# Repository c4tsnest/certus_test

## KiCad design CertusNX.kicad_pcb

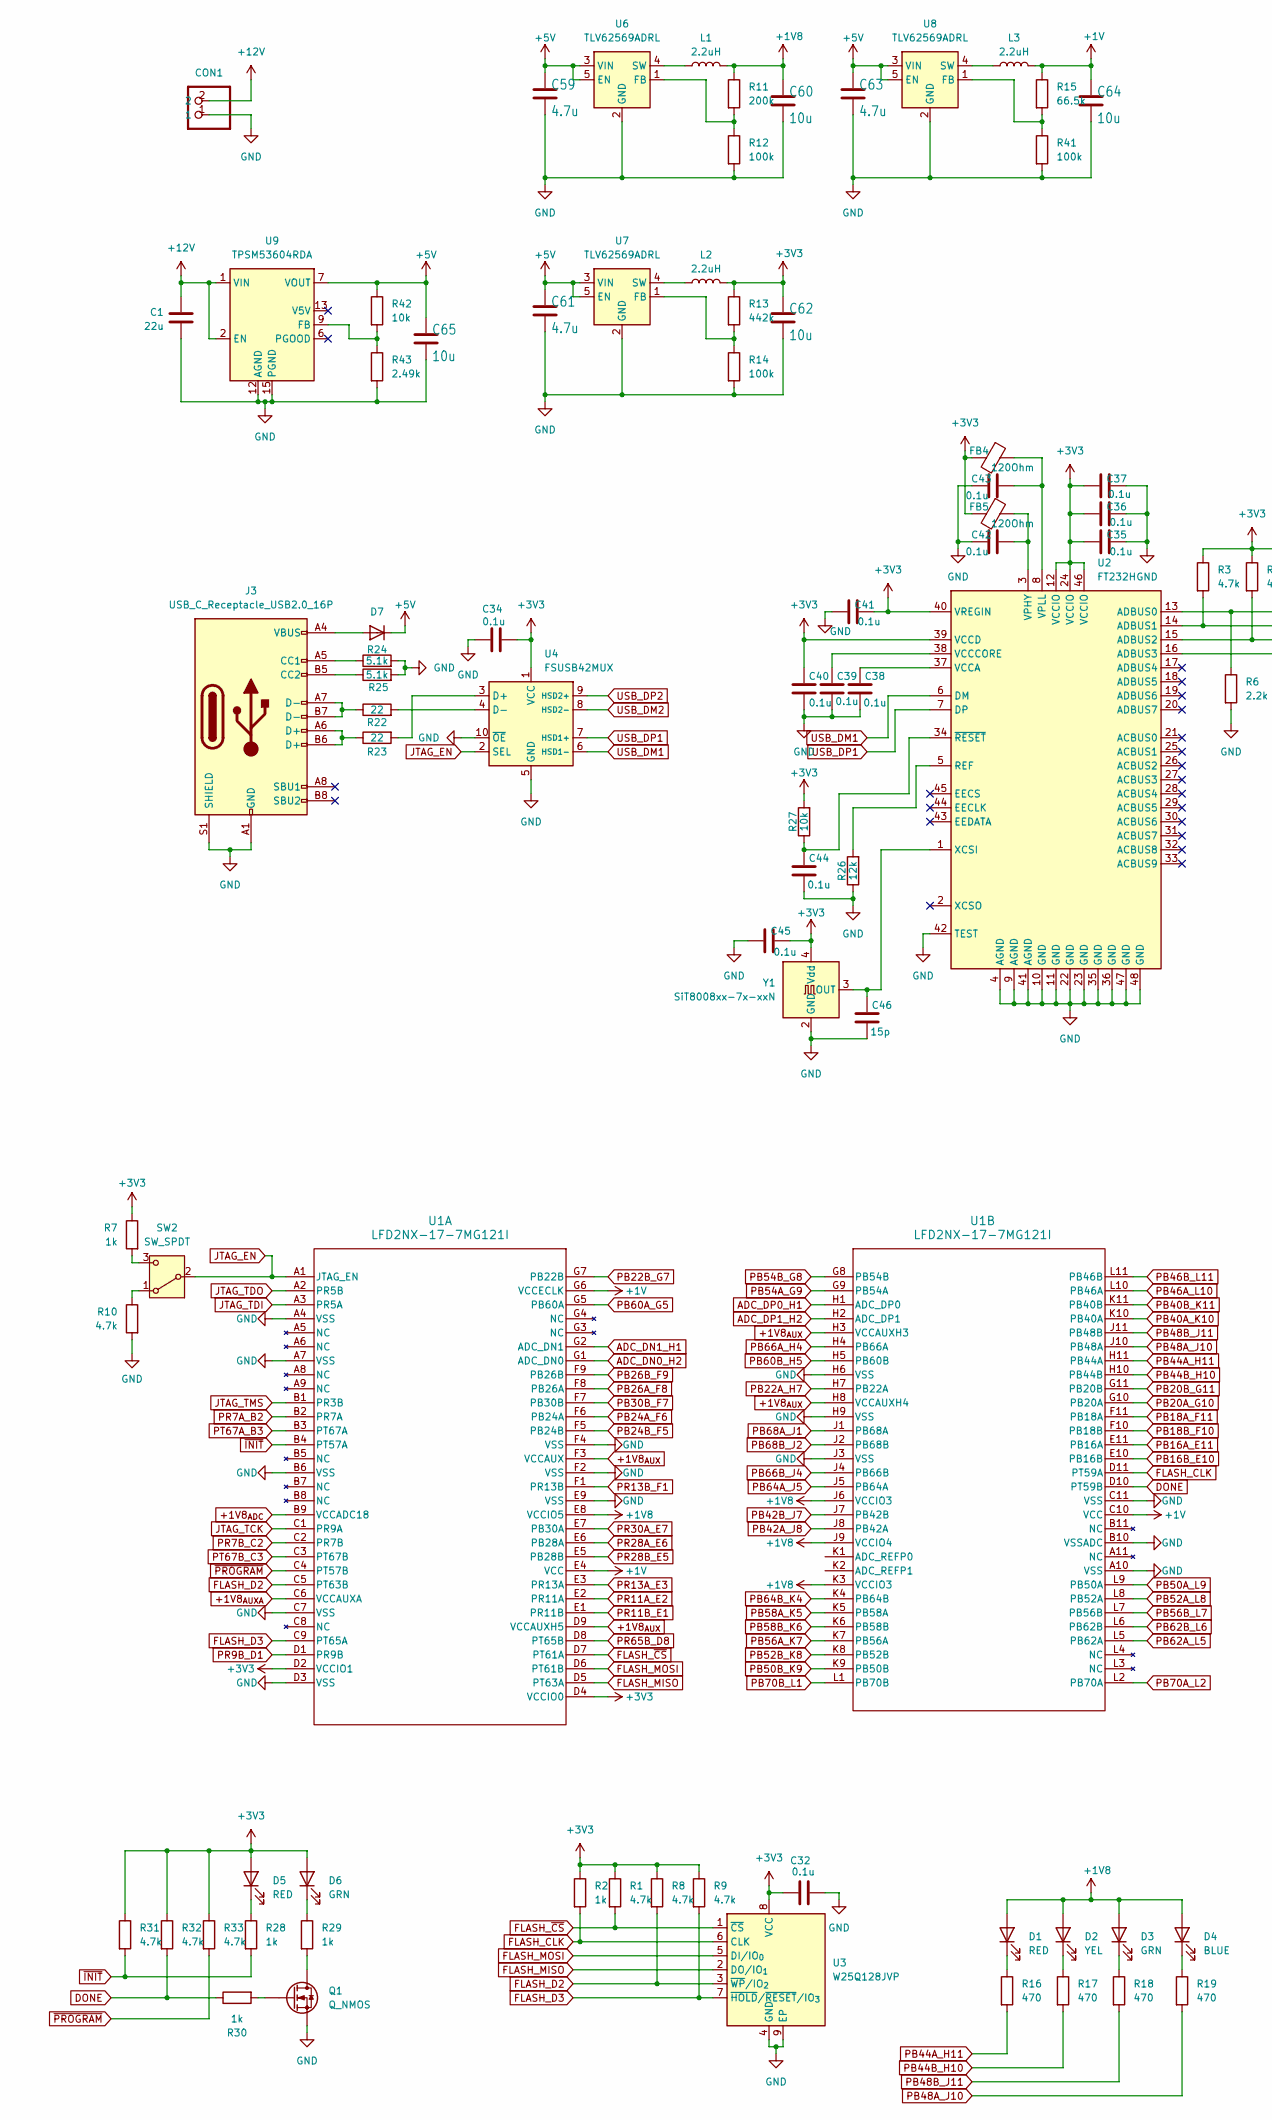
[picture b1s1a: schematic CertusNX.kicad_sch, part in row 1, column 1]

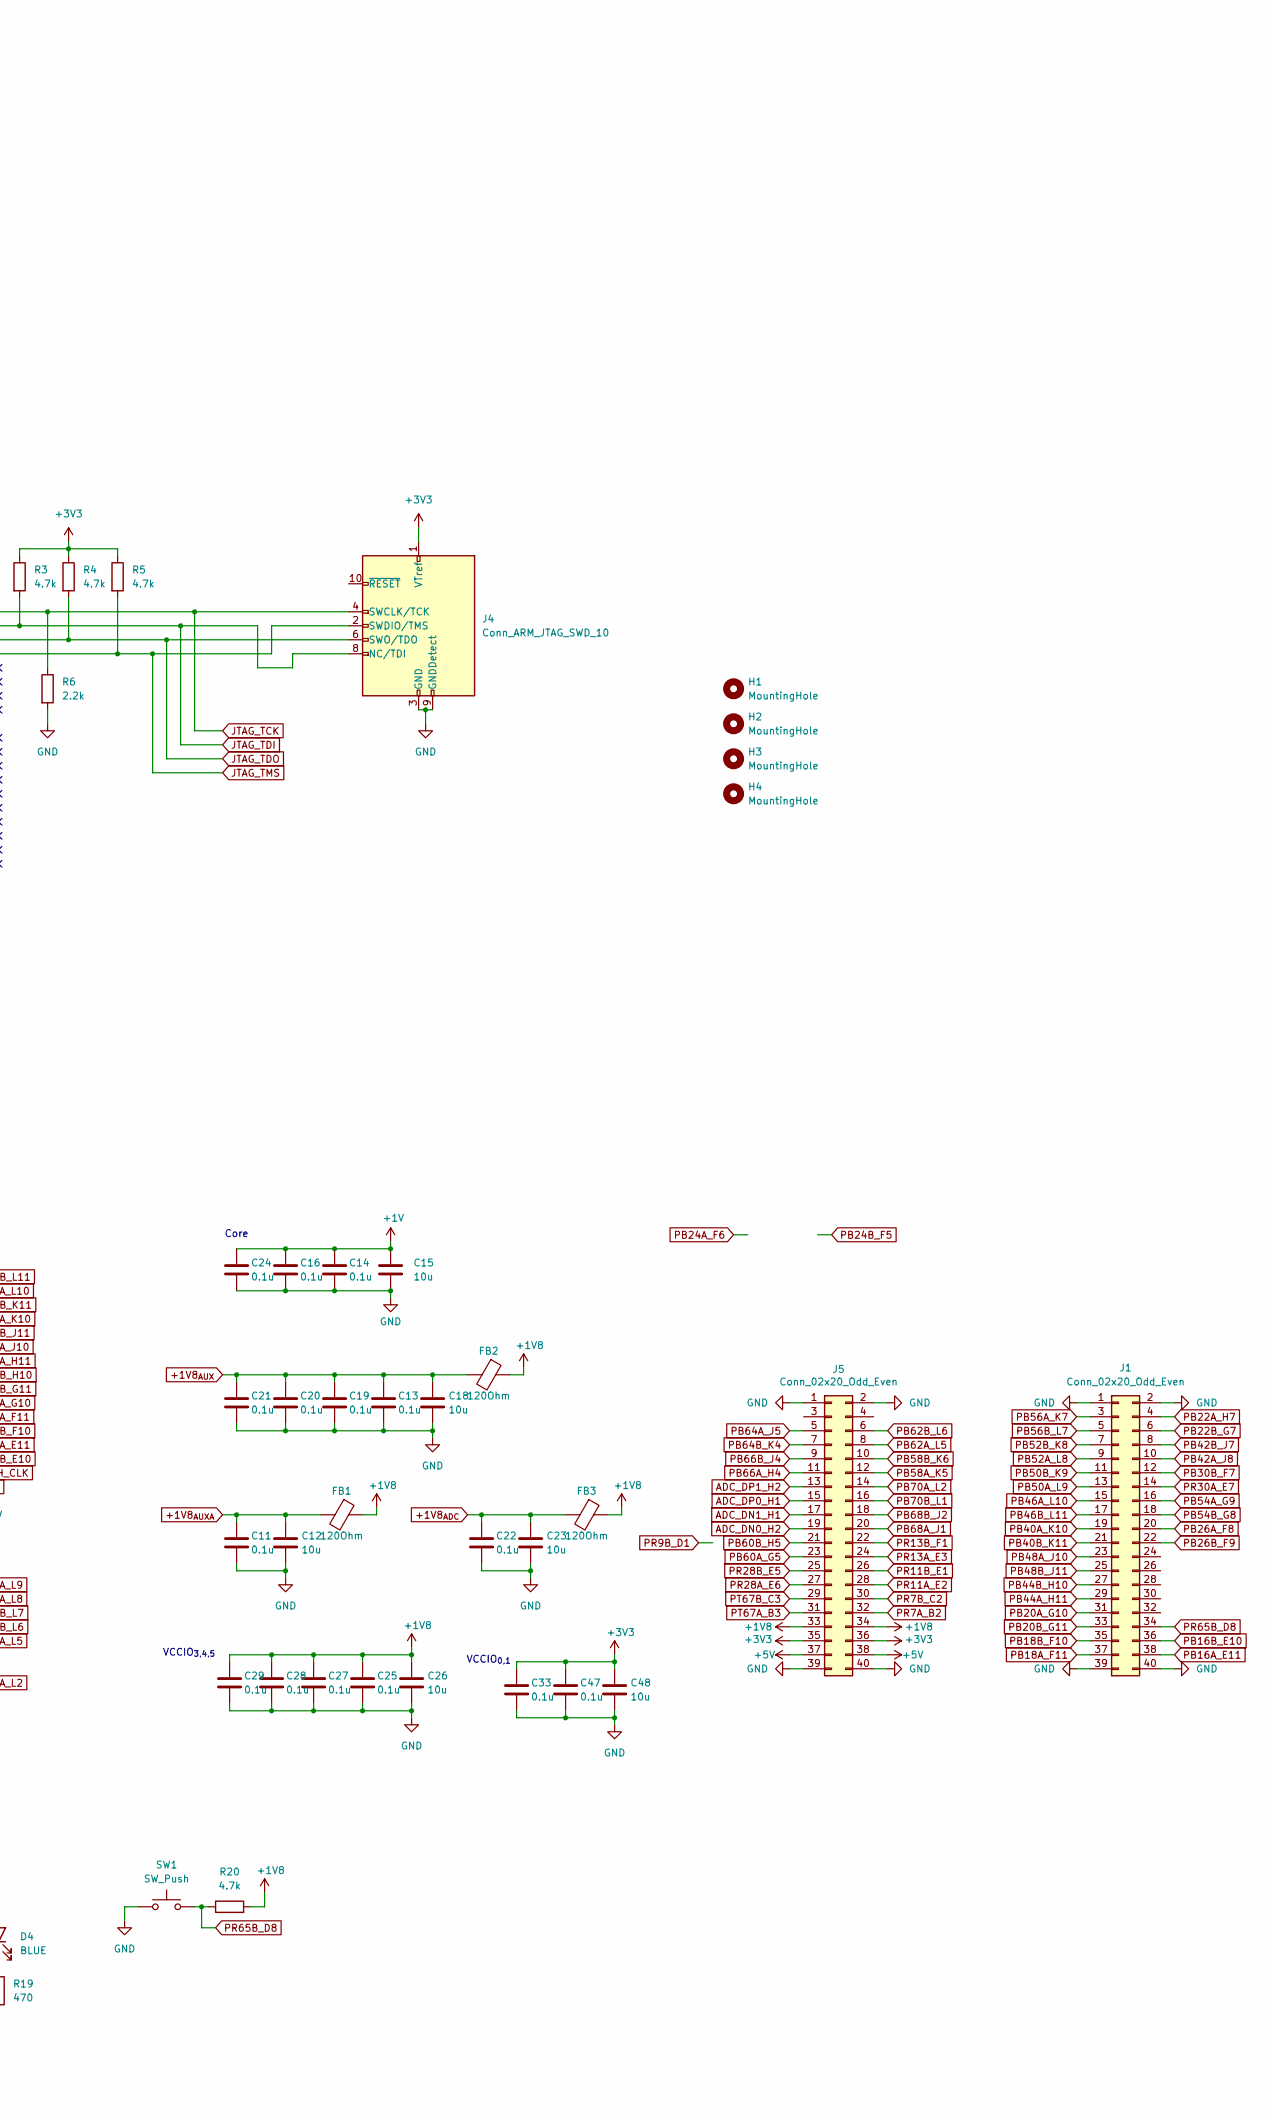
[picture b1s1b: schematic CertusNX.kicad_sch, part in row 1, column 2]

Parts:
C1: 22u; C_1206_3216Metric_Pad1.33x1.80mm_HandSolder
C11, C13, C14, C16, C19, C20, C21, C22, C24, C25, C27, C28, C29, C33, C47: 0.1u; C_0201_0603Metric
C12, C15, C18, C23, C26, C48, C60, C62, C64, C65: 10u; C_0603_1608Metric_Pad1.08x0.95mm_HandSolder
C32, C34, C35, C36, C37, C38, C39, C40, C41, C42, C43, C44, C45: 0.1u; C_0402_1005Metric_Pad0.74x0.62mm_HandSolder
C46: 15p; C_0402_1005Metric_Pad0.74x0.62mm_HandSolder
C59, C61, C63: 4.7u; C_0603_1608Metric_Pad1.08x0.95mm_HandSolder
CON1: Molex_Nano-Fit_105309-xx02_1x02_P2.50mm_Vertical
D1, D5: RED; LED_0402_1005Metric_Pad0.77x0.64mm_HandSolder
D2: YEL; LED_0402_1005Metric_Pad0.77x0.64mm_HandSolder
D3, D6: GRN; LED_0402_1005Metric_Pad0.77x0.64mm_HandSolder
D4: BLUE; LED_0402_1005Metric_Pad0.77x0.64mm_HandSolder
D7: SOD-123
FB1, FB2, FB3, FB4, FB5: 120Ohm; L_0603_1608Metric_Pad1.05x0.95mm_HandSolder
H1, H2, H3, H4: MountingHole; MountingHole_3.2mm_M3
J1, J5: Conn_02x20_Odd_Even; Molex_SlimStack_52991-0408_2x20_P0.50mm_Vertical
J3: USB_C_Receptacle_USB2.0_16P; USB_C_Receptacle_GCT_USB4105-xx-A_16P_TopMnt_Horizontal
J4: Conn_ARM_JTAG_SWD_10; PinHeader_2x05_P1.27mm_Vertical
L1, L2, L3: 2.2uH; L_1210_3225Metric_Pad1.42x2.65mm_HandSolder
Q1: Q_NMOS; SOT-416
R1, R3, R4, R5, R8, R9, R10, R20, R31, R32, R33: 4.7k; R_0402_1005Metric_Pad0.72x0.64mm_HandSolder
R2, R7, R28, R29, R30: 1k; R_0402_1005Metric_Pad0.72x0.64mm_HandSolder
R6: 2.2k; R_0402_1005Metric_Pad0.72x0.64mm_HandSolder
R11: 200k; R_0402_1005Metric_Pad0.72x0.64mm_HandSolder
R12, R14, R41: 100k; R_0402_1005Metric_Pad0.72x0.64mm_HandSolder
R13: 442k; R_0402_1005Metric_Pad0.72x0.64mm_HandSolder
R15: 66.5k; R_0402_1005Metric_Pad0.72x0.64mm_HandSolder
R16, R17, R18, R19: 470; R_0402_1005Metric_Pad0.72x0.64mm_HandSolder
R22, R23: 22; R_0402_1005Metric_Pad0.72x0.64mm_HandSolder
R24, R25: 5.1k; R_0402_1005Metric_Pad0.72x0.64mm_HandSolder
R26: 12k; R_0402_1005Metric_Pad0.72x0.64mm_HandSolder
R27, R42: 10k; R_0402_1005Metric_Pad0.72x0.64mm_HandSolder
R43: 2.49k; R_0402_1005Metric_Pad0.72x0.64mm_HandSolder
SW1: SW_Push; SW_SPST_B3U-1000P
SW2: SW_SPDT; SW_SPDT_PCM12
U1: LFD2NX-17-7MG121I
U2: FT232H; QFN-48-1EP_8x8mm_P0.5mm_EP6.2x6.2mm
U3: W25Q128JVP; WSON-8-1EP_6x5mm_P1.27mm_EP3.4x4.3mm
U4: FSUSB42MUX; FSUSB42UMX
U6, U7, U8: TLV62569ADRL; SOT-563
U9: TPSM53604RDA; Texas_B3QFN-14-1EP_5x5.5mm_P0.65mm_ThermalVia
Y1: SiT8008xx-7x-xxN; Oscillator_SMD_SiT_PQFN-4Pin_2.0x1.6mm

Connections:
+1V: C14.1, C15.1, C16.1, C24.1, C64.1, L3.2, R15.1, U1.C10 (VCC), U1.E4 (VCC), U1.G6 (VCCECLK)
+1V8: C25.1, C26.1, C27.1, C28.1, C29.1, C60.1, D1.2 (A), D2.2 (A), D3.2 (A), D4.2 (A), FB1.1, FB2.1, FB3.1, J5.33, J5.34, L1.2, R11.1, R20.2, U1.E8 (VCCIO5), U1.J6 (VCCIO3), U1.J9 (VCCIO4), U1.K3 (VCCIO3)
+1V8_{ADC}: C22.1, C23.1, FB3.2, U1.B9 (VCCADC18)
+1V8_{AUXA}: C11.1, C12.1, FB1.2, U1.C6 (VCCAUXA)
+1V8_{AUX}: C13.1, C18.1, C19.1, C20.1, C21.1, FB2.2, U1.D9 (VCCAUXH5), U1.F3 (VCCAUX), U1.H3 (VCCAUXH3), U1.H8 (VCCAUXH4)
+3V3: C32.1, C33.1, C34.2, C35.1, C36.1, C37.1, C40.1, C41.2, C45.2, C47.1, C48.1, C62.1, D5.2 (A), D6.2 (A), FB4.2, FB5.2, J4.1 (VTref), J5.35, J5.36, L2.2, R1.1, R2.1, R3.1, R4.1, R5.1, R7.1, R8.1, R9.1, R13.1, R27.2, R31.1, R32.1, R33.1, U1.D2 (VCCIO1), U1.D4 (VCCIO0), U2.12 (VCCIO), U2.24 (VCCIO), U2.39 (VCCD), U2.40 (VREGIN), U2.46 (VCCIO), U3.8 (VCC), U4.1 (VCC), Y1.4 (Vdd)
+5V: C59.1, C61.1, C63.1, C65.1, D7.K (C), J5.37, J5.38, R42.1, U6.3 (VIN), U6.5 (EN), U7.3 (VIN), U7.5 (EN), U8.3 (VIN), U8.5 (EN), U9.7 (VOUT), U9.8 (VOUT)
+12V: C1.1, CON1.2, U9.1 (VIN), U9.2 (EN), U9.14 (VIN)
ADC_DN0_H2: J5.19, U1.G1 (ADC_DN0)
ADC_DN1_H1: J5.17, U1.G2 (ADC_DN1)
ADC_DP0_H1: J5.15, U1.H1 (ADC_DP0)
ADC_DP1_H2: J5.13, U1.H2 (ADC_DP1)
DONE: R30.1, R32.2, U1.D10 (PT59B)
FLASH_CLK: R2.2, U1.D11 (PT59A), U3.6 (CLK)
FLASH_D2: R8.2, U1.C5 (PT63B), U3.3 (~WP/IO_{2})
FLASH_D3: R9.2, U1.C9 (PT65A), U3.7 (~HOLD/~RESET/IO_{3})
FLASH_MISO: U1.D5 (PT63A), U3.2 (DO/IO_{1})
FLASH_MOSI: U1.D6 (PT61B), U3.5 (DI/IO_{0})
FLASH_~CS: R1.2, U1.D7 (PT61A), U3.1 (~CS)
GND: C1.2, C11.2, C12.2, C13.2, C14.2, C15.2, C16.2, C18.2, C19.2, C20.2, C21.2, C22.2, C23.2, C24.2, C25.2, C26.2, C27.2, C28.2, C29.2, C32.2, C33.2, C34.1, C35.2, C36.2, C37.2, C38.2, C39.2, C40.2, C41.1, C42.2, C43.2, C44.2, C45.1, C46.2, C47.2, C48.2, C59.2, C60.2, C61.2, C62.2, C63.2, C64.2, C65.2, CON1.1, J1.1, J1.2, J1.39, J1.40, J3.A1 (GND), J3.A12 (GND), J3.B1 (GND), J3.B12 (GND), J3.S1 (SHIELD), J4.3 (GND), J4.5 (GND), J4.9 (GNDDetect), J5.1, J5.2, J5.39, J5.40, Q1.2 (S), Q1.S, R6.2, R10.2, R12.2, R14.2, R24.2, R25.2, R26.1, R41.2, R43.2, SW1.1, U1.A4 (VSS), U1.A7 (VSS), U1.A10 (VSS), U1.B6 (VSS), U1.B10 (VSSADC), U1.C7 (VSS), U1.C11 (VSS), U1.D3 (VSS), U1.E9 (VSS), U1.F2 (VSS), U1.F4 (VSS), U1.H6 (VSS), U1.H9 (VSS), U1.J3 (VSS), U2.4 (AGND), U2.9 (AGND), U2.10 (GND), U2.11 (GND), U2.22 (GND), U2.23 (GND), U2.35 (GND), U2.36 (GND), U2.41 (AGND), U2.42 (TEST), U2.47 (GND), U2.48 (GND), U3.4 (GND), U3.9 (EP), U4.5 (GND), U4.10 (~OE), U6.2 (GND), U7.2 (GND), U8.2 (GND), U9.3 (PGND), U9.10 (PGND), U9.11 (PGND), U9.12 (AGND), U9.15 (PGND), Y1.2 (GND)
JTAG_EN: SW2.2 (B), U1.A1 (JTAG_EN), U4.2 (SEL)
JTAG_TCK: J4.4 (SWCLK/TCK), R6.1, U1.C1 (PR9A), U2.13 (ADBUS0)
JTAG_TDI: J4.8 (NC/TDI), R3.2, U1.A3 (PR5A), U2.14 (ADBUS1)
JTAG_TDO: J4.6 (SWO/TDO), R4.2, U1.A2 (PR5B), U2.15 (ADBUS2)
JTAG_TMS: J4.2 (SWDIO/TMS), R5.2, U1.B1 (PR3B), U2.16 (ADBUS3)
unnamed: D1.1 (K), R16.1
unnamed: D2.1 (K), R17.1
unnamed: D3.1 (K), R18.1
unnamed: D4.1 (K), R19.1
unnamed: D5.1 (K), R28.1
unnamed: D6.1 (K), R29.1
unnamed: D7.A, J3.A4 (VBUS), J3.A9 (VBUS), J3.B4 (VBUS), J3.B9 (VBUS)
unnamed: J3.A5 (CC1), R24.1
unnamed: J3.B5 (CC2), R25.1
unnamed: J3.A6 (D+), J3.B6 (D+), R23.1
unnamed: J3.A7 (D-), J3.B7 (D-), R22.1
unnamed: Q1.3 (D), Q1.D, R29.2
unnamed: Q1.1 (G), Q1.G, R30.2
unnamed: R10.1, SW2.1 (A)
unnamed: R7.2, SW2.3 (C)
unnamed: R26.2, U2.5 (REF)
unnamed: C38.1, U2.37 (VCCA)
unnamed: C39.1, U2.38 (VCCCORE)
unnamed: C42.1, FB5.1, U2.3 (VPHY)
unnamed: C43.1, FB4.1, U2.8 (VPLL)
unnamed: C46.1, U2.1 (XCSI), Y1.3 (OUT)
unnamed: C44.1, R27.1, U2.34 (~RESET)
unnamed: R23.2, U4.3 (D+)
unnamed: R22.2, U4.4 (D-)
unnamed: R11.2, R12.1, U6.1 (FB)
unnamed: L1.1, U6.4 (SW)
unnamed: R13.2, R14.1, U7.1 (FB)
unnamed: L2.1, U7.4 (SW)
unnamed: R15.2, R41.1, U8.1 (FB)
unnamed: L3.1, U8.4 (SW)
unnamed: R42.2, R43.1, U9.9 (FB)
PB16A_E11: J1.38, U1.E11 (PB16A)
PB16B_E10: J1.36, U1.E10 (PB16B)
PB18A_F11: J1.37, U1.F11 (PB18A)
PB18B_F10: J1.35, U1.F10 (PB18B)
PB20A_G10: J1.31, U1.G10 (PB20A)
PB20B_G11: J1.33, U1.G11 (PB20B)
PB22A_H7: J1.4, U1.H7 (PB22A)
PB22B_G7: J1.6, U1.G7 (PB22B)
PB24A_F6: U1.F6 (PB24A)
PB24B_F5: U1.F5 (PB24B)
PB26A_F8: J1.20, U1.F8 (PB26A)
PB26B_F9: J1.22, U1.F9 (PB26B)
PB30B_F7: J1.12, U1.F7 (PB30B)
PB40A_K10: J1.19, U1.K10 (PB40A)
PB40B_K11: J1.21, U1.K11 (PB40B)
PB42A_J8: J1.10, U1.J8 (PB42A)
PB42B_J7: J1.8, U1.J7 (PB42B)
PB44A_H11: J1.29, R16.2, U1.H11 (PB44A)
PB44B_H10: J1.27, R17.2, U1.H10 (PB44B)
PB46A_L10: J1.15, U1.L10 (PB46A)
PB46B_L11: J1.17, U1.L11 (PB46B)
PB48A_J10: J1.23, R19.2, U1.J10 (PB48A)
PB48B_J11: J1.25, R18.2, U1.J11 (PB48B)
PB50A_L9: J1.13, U1.L9 (PB50A)
PB50B_K9: J1.11, U1.K9 (PB50B)
PB52A_L8: J1.9, U1.L8 (PB52A)
PB52B_K8: J1.7, U1.K8 (PB52B)
PB54A_G9: J1.16, U1.G9 (PB54A)
PB54B_G8: J1.18, U1.G8 (PB54B)
PB56A_K7: J1.3, U1.K7 (PB56A)
PB56B_L7: J1.5, U1.L7 (PB56B)
PB58A_K5: J5.12, U1.K5 (PB58A)
PB58B_K6: J5.10, U1.K6 (PB58B)
PB60A_G5: J5.23, U1.G5 (PB60A)
PB60B_H5: J5.21, U1.H5 (PB60B)
PB62A_L5: J5.8, U1.L5 (PB62A)
PB62B_L6: J5.6, U1.L6 (PB62B)
PB64A_J5: J5.5, U1.J5 (PB64A)
PB64B_K4: J5.7, U1.K4 (PB64B)
PB66A_H4: J5.11, U1.H4 (PB66A)
PB66B_J4: J5.9, U1.J4 (PB66B)
PB68A_J1: J5.20, U1.J1 (PB68A)
PB68B_J2: J5.18, U1.J2 (PB68B)
PB70A_L2: J5.14, U1.L2 (PB70A)
PB70B_L1: J5.16, U1.L1 (PB70B)
PR7A_B2: J5.32, U1.B2 (PR7A)
PR7B_C2: J5.30, U1.C2 (PR7B)
PR9B_D1: U1.D1 (PR9B)
PR11A_E2: J5.28, U1.E2 (PR11A)
PR11B_E1: J5.26, U1.E1 (PR11B)
PR13A_E3: J5.24, U1.E3 (PR13A)
PR13B_F1: J5.22, U1.F1 (PR13B)
PR28A_E6: J5.27, U1.E6 (PB28A)
PR28B_E5: J5.25, U1.E5 (PB28B)
PR30A_E7: J1.14, U1.E7 (PB30A)
PR65B_D8: J1.34, R20.1, SW1.2, U1.D8 (PT65B)
PT67A_B3: J5.31, U1.B3 (PT67A)
PT67B_C3: J5.29, U1.C3 (PT67B)
USB_DM1: U2.6 (DM), U4.6 (HSD1-)
USB_DM2: U4.8 (HSD2-)
USB_DP1: U2.7 (DP), U4.7 (HSD1+)
USB_DP2: U4.9 (HSD2+)
~INIT: R28.2, R31.2, U1.B4 (PT57A)
~PROGRAM: R33.2, U1.C4 (PT57B)

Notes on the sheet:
VCCIO_{3,4,5}
Core
VCCIO_{0,1}

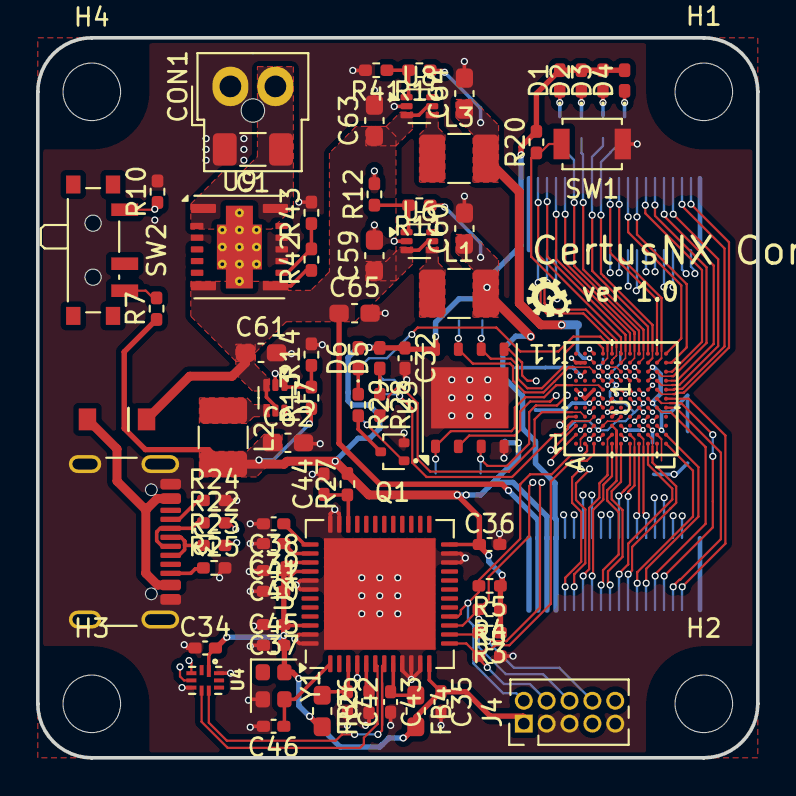
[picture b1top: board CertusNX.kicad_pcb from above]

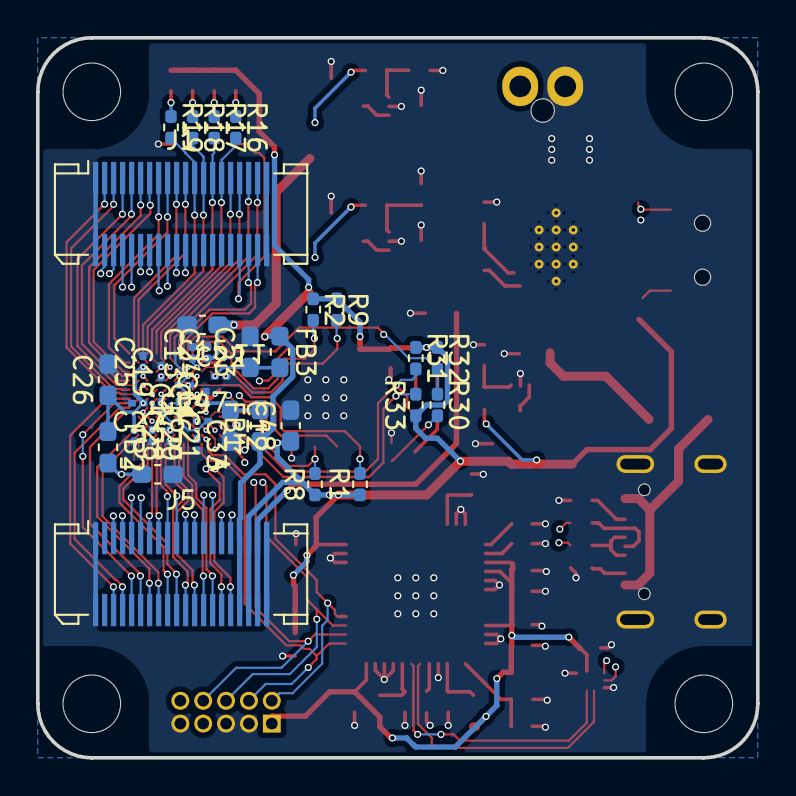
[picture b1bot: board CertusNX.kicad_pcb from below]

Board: 4 copper layers, 40.0 x 40.0 mm, 114 parts (38 on the bottom side), 115 nets.

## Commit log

2025-08-19 init
2025-08-22 配置(あきらめ)
2025-08-27 pin仮
2025-08-30 breakout
2025-08-31 配置変更
